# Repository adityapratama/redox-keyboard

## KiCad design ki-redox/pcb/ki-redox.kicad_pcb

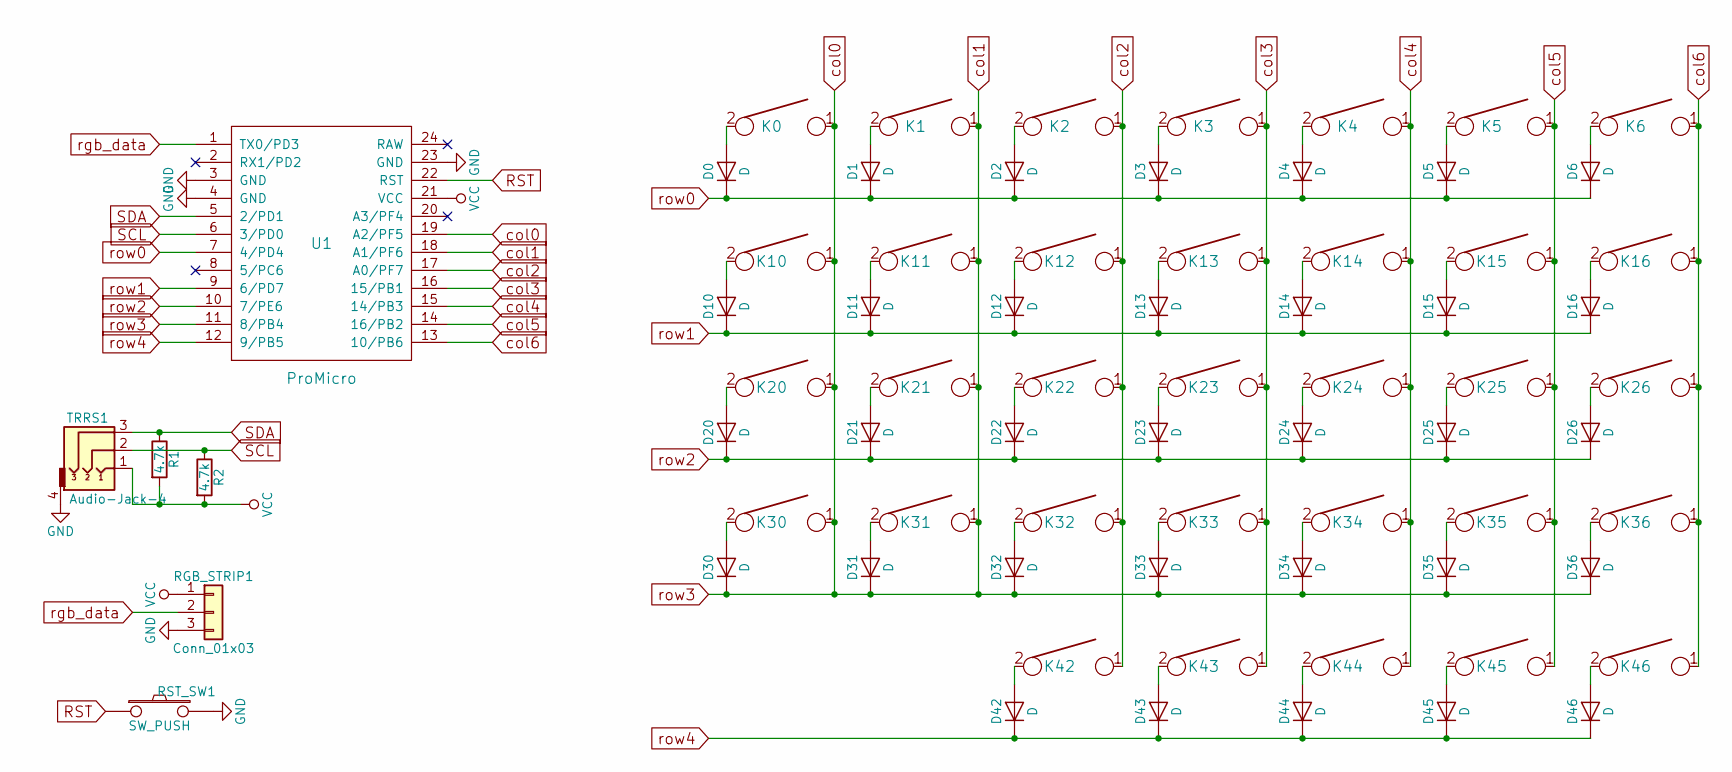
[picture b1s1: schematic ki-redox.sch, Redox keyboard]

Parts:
D0, D1, D2, D3, D4, D5, D6, D10, D11, D12, D13, D14, D15, D16, D20, D21, D22, D23, D24, D25, D26, D30, D31, D32, D33, D34, D35, D36, D42, D43, D44, D45, D46: D; Diode-dual
K0, K1, K2, K3, K4, K5, K6, K10, K11, K12, K13, K14, K15, K16, K20, K21, K22, K23, K24, K25, K26, K30, K31, K32, K33, K34, K35, K36, K42, K43, K44, K45, K46: KEYSW; Hybrid_PCB_100H_Dual_hole-nosilk
R1, R2: 4.7k; Resistor-Compact
RGB_STRIP1: Conn_01x03; Pin_Header_Straight_1x03_Pitch2.54mm
RST_SW1: SW_PUSH; SW_PUSH_6mm_h4.3mm
TRRS1: Audio-Jack-4; TRRS-PJ-320A-dual
U1: ProMicro; ArduinoProMicro

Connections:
GND: RGB_STRIP1.3, RST_SW1.2, TRRS1.4, U1.3 (GND), U1.4 (GND), U1.23 (GND)
unnamed: D0.2 (A), K0.2
unnamed: D1.2 (A), K1.2
unnamed: D2.2 (A), K2.2
unnamed: D3.2 (A), K3.2
unnamed: D4.2 (A), K4.2
unnamed: D5.2 (A), K5.2
unnamed: D6.2 (A), K6.2
unnamed: D10.2 (A), K10.2
unnamed: D11.2 (A), K11.2
unnamed: D12.2 (A), K12.2
unnamed: D13.2 (A), K13.2
unnamed: D14.2 (A), K14.2
unnamed: D15.2 (A), K15.2
unnamed: D16.2 (A), K16.2
unnamed: D20.2 (A), K20.2
unnamed: D21.2 (A), K21.2
unnamed: D22.2 (A), K22.2
unnamed: D23.2 (A), K23.2
unnamed: D24.2 (A), K24.2
unnamed: D25.2 (A), K25.2
unnamed: D26.2 (A), K26.2
unnamed: D30.2 (A), K30.2
unnamed: D31.2 (A), K31.2
unnamed: D32.2 (A), K32.2
unnamed: D33.2 (A), K33.2
unnamed: D34.2 (A), K34.2
unnamed: D35.2 (A), K35.2
unnamed: D36.2 (A), K36.2
unnamed: D42.2 (A), K42.2
unnamed: D43.2 (A), K43.2
unnamed: D44.2 (A), K44.2
unnamed: D45.2 (A), K45.2
unnamed: D46.2 (A), K46.2
RST: RST_SW1.1, U1.22 (RST)
SCL: R2.1, TRRS1.2, U1.6 (3/PD0)
SDA: R1.1, TRRS1.3, U1.5 (2/PD1)
VCC: R1.2, R2.2, RGB_STRIP1.1, TRRS1.1, U1.21 (VCC)
col2: K2.1, K12.1, K22.1, K32.1, K42.1, U1.17 (A0/PF7)
col3: K3.1, K13.1, K23.1, K33.1, K43.1, U1.16 (15/PB1)
col4: K4.1, K14.1, K24.1, K34.1, K44.1, U1.15 (14/PB3)
col5: K5.1, K15.1, K25.1, K35.1, K45.1, U1.14 (16/PB2)
col6: K6.1, K16.1, K26.1, K36.1, K46.1, U1.13 (10/PB6)
rgb_data: RGB_STRIP1.2, U1.1 (TX0/PD3)
row0: D0.1 (K), D1.1 (K), D2.1 (K), D3.1 (K), D4.1 (K), D5.1 (K), D6.1 (K), U1.7 (4/PD4)
row1: D10.1 (K), D11.1 (K), D12.1 (K), D13.1 (K), D14.1 (K), D15.1 (K), D16.1 (K), U1.9 (6/PD7)
row2: D20.1 (K), D21.1 (K), D22.1 (K), D23.1 (K), D24.1 (K), D25.1 (K), D26.1 (K), U1.10 (7/PE6)
row4: D42.1 (K), D43.1 (K), D44.1 (K), D45.1 (K), D46.1 (K), U1.12 (9/PB5)

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
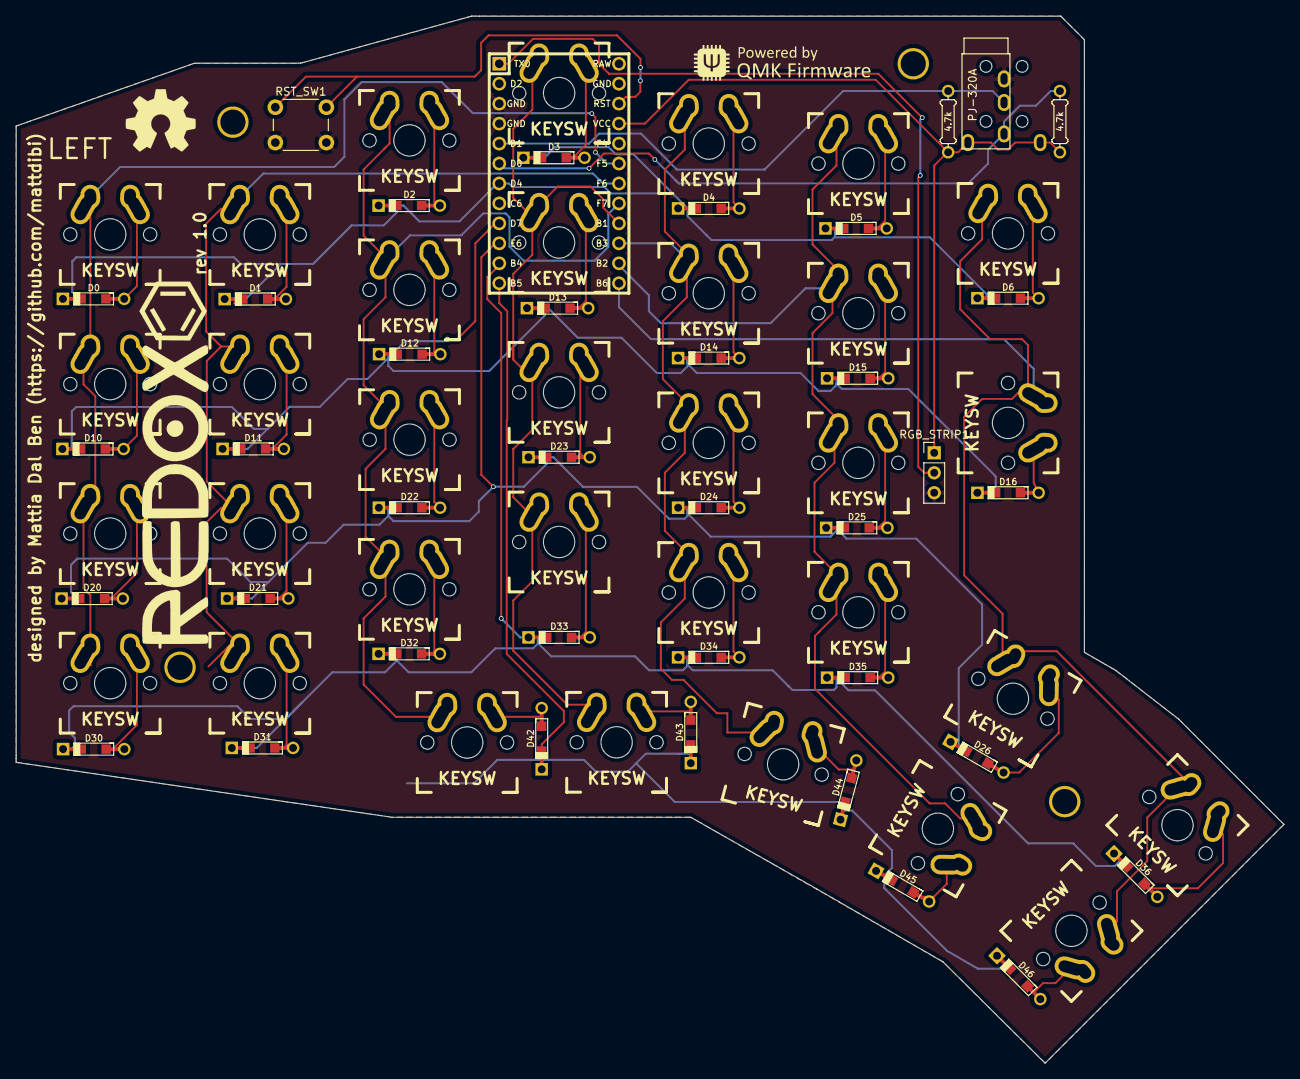
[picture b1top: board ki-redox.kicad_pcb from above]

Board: 2 copper layers, 161.4 x 133.3 mm, 76 parts (0 on the bottom side), 51 nets.

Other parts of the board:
HOLE_M3, HOLE_M3#2, HOLE_M3#3, HOLE_M3#4: VAL**; HOLE_M3

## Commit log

2020-12-10 Add ki-redox
